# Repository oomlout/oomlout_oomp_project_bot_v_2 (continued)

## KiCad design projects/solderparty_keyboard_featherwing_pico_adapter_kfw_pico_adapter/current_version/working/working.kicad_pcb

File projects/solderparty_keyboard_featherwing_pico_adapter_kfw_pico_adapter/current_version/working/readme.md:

# keyboard_featherwing_pico_adapter
 
## summary 
* id: solderparty_keyboard_featherwing_pico_adapter_kfw_pico_adapter
* user: solderparty
* name: keyboard_featherwing_pico_adapter
* board: kfw_pico_adapter
* repo: https://github.com/solderparty/keyboard_featherwing_pico_adapter
* src_file_repo_kicad_pcb: kfw_pico_adapter.kicad_pcb
* src_file_repo_kicad_pcb_link: https://github.com/solderparty/keyboard_featherwing_pico_adapter/tree/main/kfw_pico_adapter.kicad_pcb
* src_file_repo_kicad_sch: kfw_pico_adapter.kicad_sch
* src_file_repo_kicad_sch_link: https://github.com/solderparty/keyboard_featherwing_pico_adapter/tree/main/kfw_pico_adapter.kicad_sch

* src_file_repo_sch: 
* src_file_repo_sch_link: https://github.com/solderparty/keyboard_featherwing_pico_adapter/tree/main/
* full details link: https://github.com/oomlout/oomlout_oomp_project_bot_v_2/tree/main/projects/solderparty_keyboard_featherwing_pico_adapter_kfw_pico_adapter/current_version/working  

## schematic  
  
[schematic (pdf)](working_schematic.pdf) 

## pcb  

[board (pdf)](working.pdf)  

## working_bom
| Id | Designator | Footprint | Quantity | Designation | Supplier and ref |  | None | 
| --- | --- | --- | --- | --- | --- | --- | --- | 
| 1 | J2 | PinHeader_2x16_P2.54mm_Vertical | 1 | Conn_Left |  |  | [''] | 
| 2 | J3 | PinHeader_2x12_P2.54mm_Vertical | 1 | Conn_Right |  |  | [''] | 
| 3 | G*** | SolderParty-New-Logo_15x12.7mm_SilkScreen | 1 | LOGO |  |  | [''] | 
| 4 | U1 | RaspberryPi_Pico | 1 | RaspberryPi_Pico |  |  | [''] | 
| 5 | G*** | SolderParty-New-Logo_7.5x6.4mm_SilkScreen | 1 | LOGO |  |  | [''] | 

## bom_schematic
| Ref | Qnty | Value | Cmp name | Footprint | Description | Vendor | DNP | 
| --- | --- | --- | --- | --- | --- | --- | --- | 
| J2 | 1 | Conn_Left | Conn_02x16_Odd_Even | Connector_PinHeader_2.54mm:PinHeader_2x16_P2.54mm_Vertical | Generic connector, double row, 02x16, odd/even pin numbering scheme (row 1 odd numbers, row 2 even numbers), script generated (kicad-library-utils/schlib/autogen/connector/) |  |  | 
| J3 | 1 | Conn_Right | Conn_02x12_Odd_Even | Connector_PinHeader_2.54mm:PinHeader_2x12_P2.54mm_Vertical | Generic connector, double row, 02x12, odd/even pin numbering scheme (row 1 odd numbers, row 2 even numbers), script generated (kicad-library-utils/schlib/autogen/connector/) |  |  | 
| U1 | 1 | RaspberryPi_Pico | RaspberryPi_Pico | Module_Extra:RaspberryPi_Pico |  |  |  |

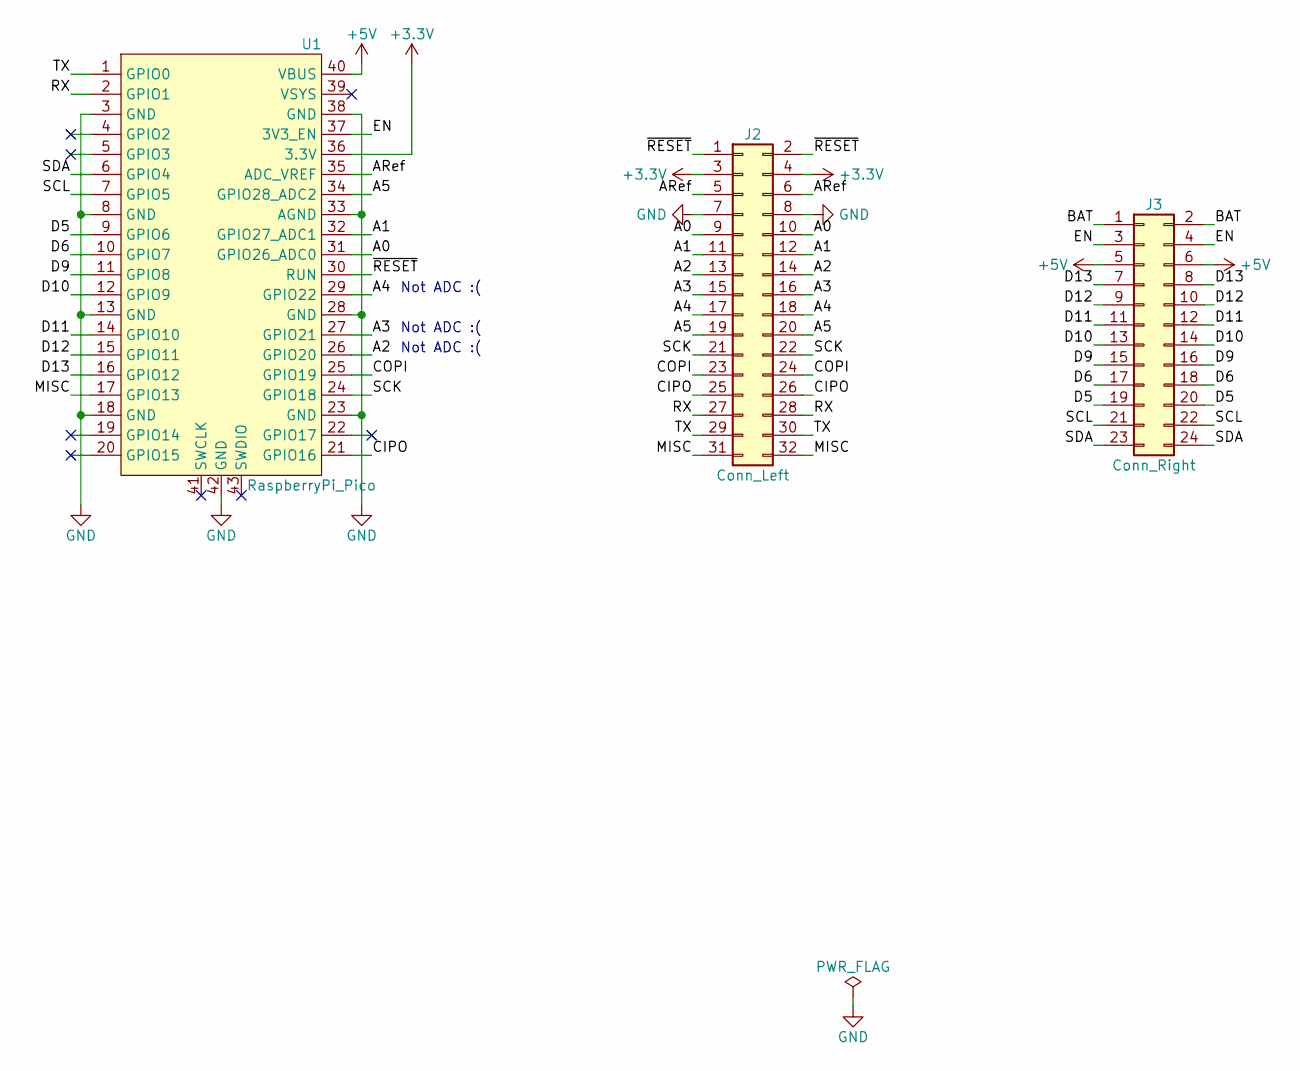
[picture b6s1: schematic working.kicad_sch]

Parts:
J2: Conn_Left; PinHeader_2x16_P2.54mm_Vertical
J3: Conn_Right; PinHeader_2x12_P2.54mm_Vertical
U1: RaspberryPi_Pico

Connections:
+3V3: J2.3, J2.4, U1.36 (3.3V)
+5V: J3.5, J3.6, U1.40 (VBUS)
/A0: J2.9, J2.10, U1.31 (GPIO26_ADC0)
/A1: J2.11, J2.12, U1.32 (GPIO27_ADC1)
/A2: J2.13, J2.14, U1.26 (GPIO20)
/A3: J2.15, J2.16, U1.27 (GPIO21)
/A4: J2.17, J2.18, U1.29 (GPIO22)
/A5: J2.19, J2.20, U1.34 (GPIO28_ADC2)
/ARef: J2.5, J2.6, U1.35 (ADC_VREF)
/BAT: J3.1, J3.2
/CIPO: J2.25, J2.26, U1.21 (GPIO16)
/COPI: J2.23, J2.24, U1.25 (GPIO19)
/D5: J3.19, J3.20, U1.9 (GPIO6)
/D6: J3.17, J3.18, U1.10 (GPIO7)
/D9: J3.15, J3.16, U1.11 (GPIO8)
/D10: J3.13, J3.14, U1.12 (GPIO9)
/D11: J3.11, J3.12, U1.14 (GPIO10)
/D12: J3.9, J3.10, U1.15 (GPIO11)
/D13: J3.7, J3.8, U1.16 (GPIO12)
/EN: J3.3, J3.4, U1.37 (3V3_EN)
/MISC: J2.31, J2.32, U1.17 (GPIO13)
/RX: J2.27, J2.28, U1.2 (GPIO1)
/SCK: J2.21, J2.22, U1.24 (GPIO18)
/SCL: J3.21, J3.22, U1.7 (GPIO5)
/SDA: J3.23, J3.24, U1.6 (GPIO4)
/TX: J2.29, J2.30, U1.1 (GPIO0)
/~RESET: J2.1, J2.2, U1.30 (RUN)
GND: J2.7, J2.8, U1.3 (GND), U1.8 (GND), U1.13 (GND), U1.18 (GND), U1.23 (GND), U1.28 (GND), U1.33 (AGND), U1.38 (GND), U1.42 (GND)

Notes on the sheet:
Not ADC :(

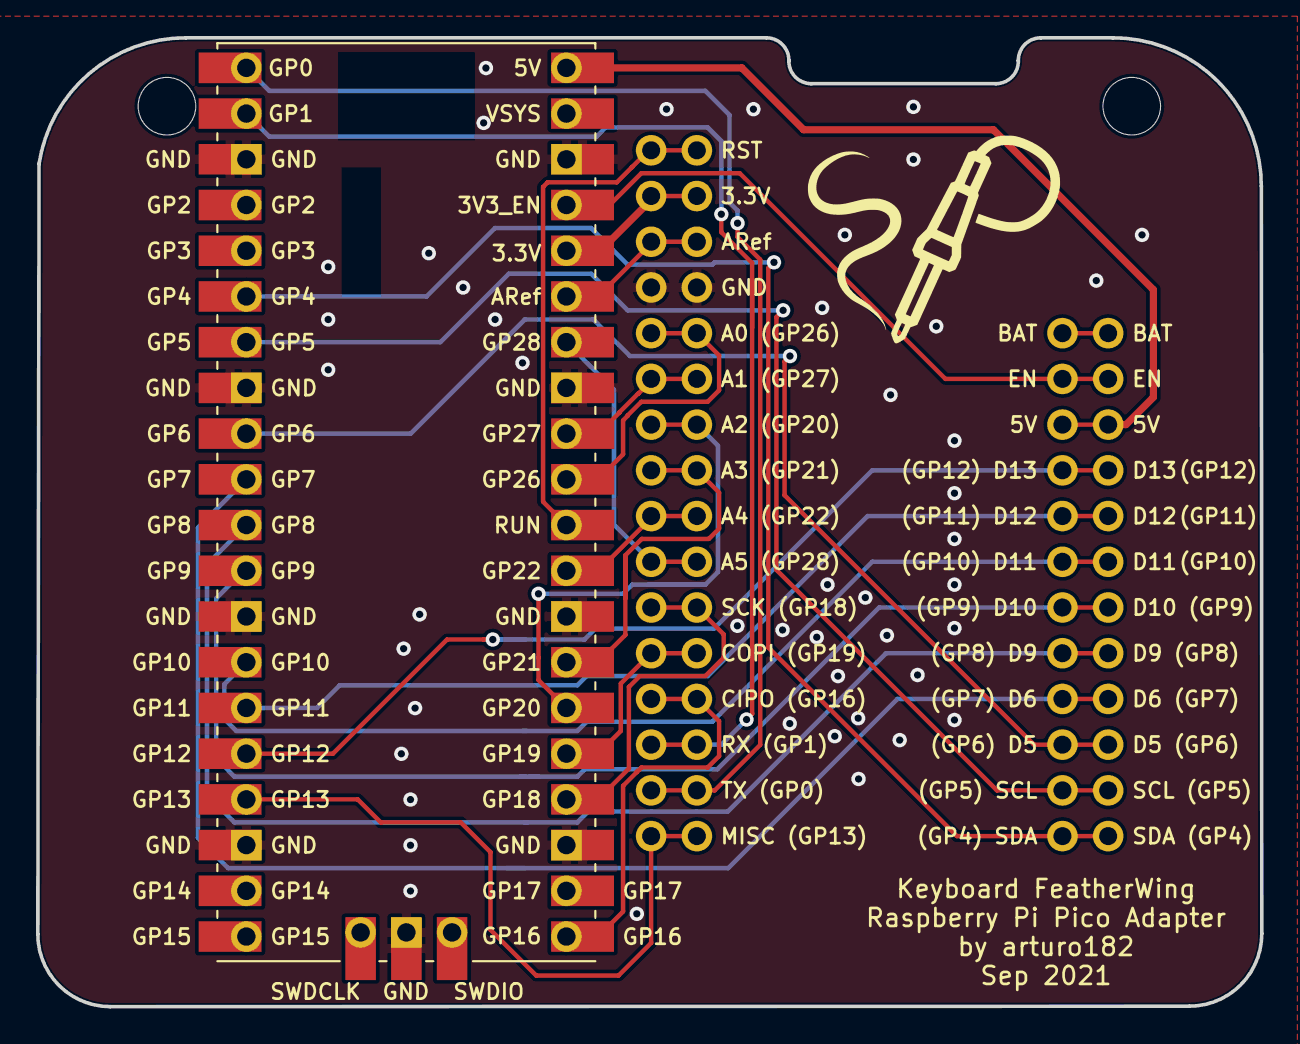
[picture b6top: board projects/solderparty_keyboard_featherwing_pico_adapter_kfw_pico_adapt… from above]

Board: 2 copper layers, 68.0 x 53.8 mm, 3 parts (0 on the bottom side), 28 nets.

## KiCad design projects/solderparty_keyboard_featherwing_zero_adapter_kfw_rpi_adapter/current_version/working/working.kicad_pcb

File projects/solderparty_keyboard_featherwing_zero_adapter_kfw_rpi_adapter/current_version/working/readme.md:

# keyboard_featherwing_zero_adapter
 
## summary 
* id: solderparty_keyboard_featherwing_zero_adapter_kfw_rpi_adapter
* user: solderparty
* name: keyboard_featherwing_zero_adapter
* board: kfw_rpi_adapter
* repo: https://github.com/solderparty/keyboard_featherwing_zero_adapter
* src_file_repo_kicad_pcb: kfw_rpi_adapter.kicad_pcb
* src_file_repo_kicad_pcb_link: https://github.com/solderparty/keyboard_featherwing_zero_adapter/tree/main/kfw_rpi_adapter.kicad_pcb
* src_file_repo_kicad_sch: kfw_rpi_adapter.kicad_sch
* src_file_repo_kicad_sch_link: https://github.com/solderparty/keyboard_featherwing_zero_adapter/tree/main/kfw_rpi_adapter.kicad_sch

* src_file_repo_sch: 
* src_file_repo_sch_link: https://github.com/solderparty/keyboard_featherwing_zero_adapter/tree/main/
* full details link: https://github.com/oomlout/oomlout_oomp_project_bot_v_2/tree/main/projects/solderparty_keyboard_featherwing_zero_adapter_kfw_rpi_adapter/current_version/working  

## schematic  
  
[schematic (pdf)](working_schematic.pdf) 

## pcb  

[board (pdf)](working.pdf)  

## working_bom
| Id | Designator | Footprint | Quantity | Designation | Supplier and ref |  | None | 
| --- | --- | --- | --- | --- | --- | --- | --- | 
| 1 | U1 | TSSOP-10_3x3mm_P0.5mm | 1 | ADS1115IDGS |  |  | [''] | 
| 2 | G***,G*** | SolderParty-New-Logo_20x16.9mm_SilkScreen | 2 | LOGO |  |  | [''] | 
| 3 | JP1 | SolderJumper-3_P1.3mm_Bridged12_RoundedPad1.0x1.5mm_NumberLabels | 1 | SJ_STM_KBD |  |  | [''] | 
| 4 | REF**,REF** | Fiducial_0.5mm_Mask1.5mm | 2 | Fiducial_0.5mm_Mask1.5mm |  |  | [''] | 
| 5 | J2 | PinHeader_2x16_P2.54mm_Vertical | 1 | Conn_Left |  |  | [''] | 
| 6 | J3 | PinHeader_2x12_P2.54mm_Vertical | 1 | Conn_Right |  |  | [''] | 
| 7 | C1 | C_0603_1608Metric | 1 | 0.1uF |  |  | [''] | 
| 8 | J1 | PinHeader_2x20_P2.54mm_Vertical | 1 | Conn_RPi |  |  | [''] | 

## bom_schematic
| Ref | Qnty | Value | Cmp name | Footprint | Description | Vendor | DNP | 
| --- | --- | --- | --- | --- | --- | --- | --- | 
| C1 | 1 | 0.1uF | C_Small | Capacitor_SMD:C_0603_1608Metric | Unpolarized capacitor, small symbol |  |  | 
| J1 | 1 | Conn_RPi | Conn_02x20_Odd_Even | Connector_PinHeader_2.54mm:PinHeader_2x20_P2.54mm_Vertical | Generic connector, double row, 02x20, odd/even pin numbering scheme (row 1 odd numbers, row 2 even numbers), script generated (kicad-library-utils/schlib/autogen/connector/) |  |  | 
| J2 | 1 | Conn_Left | Conn_02x16_Odd_Even | Connector_PinHeader_2.54mm:PinHeader_2x16_P2.54mm_Vertical | Generic connector, double row, 02x16, odd/even pin numbering scheme (row 1 odd numbers, row 2 even numbers), script generated (kicad-library-utils/schlib/autogen/connector/) |  |  | 
| J3 | 1 | Conn_Right | Conn_02x12_Odd_Even | Connector_PinHeader_2.54mm:PinHeader_2x12_P2.54mm_Vertical | Generic connector, double row, 02x12, odd/even pin numbering scheme (row 1 odd numbers, row 2 even numbers), script generated (kicad-library-utils/schlib/autogen/connector/) |  |  | 
| JP1 | 1 | SJ_STM_KBD | SolderJumper_3_Bridged12 | Jumper:SolderJumper-3_P1.3mm_Bridged12_RoundedPad1.0x1.5mm_NumberLabels | 3-pole Solder Jumper, pins 1+2 closed/bridged |  |  | 
| U1 | 1 | ADS1115IDGS | ADS1115IDGS | Package_SO:TSSOP-10_3x3mm_P0.5mm | Ultra-Small, Low-Power, I2C-Compatible, 860-SPS, 16-Bit ADCs With Internal Reference, Oscillator, and Programmable Comparator, VSSOP-10 |  |  |

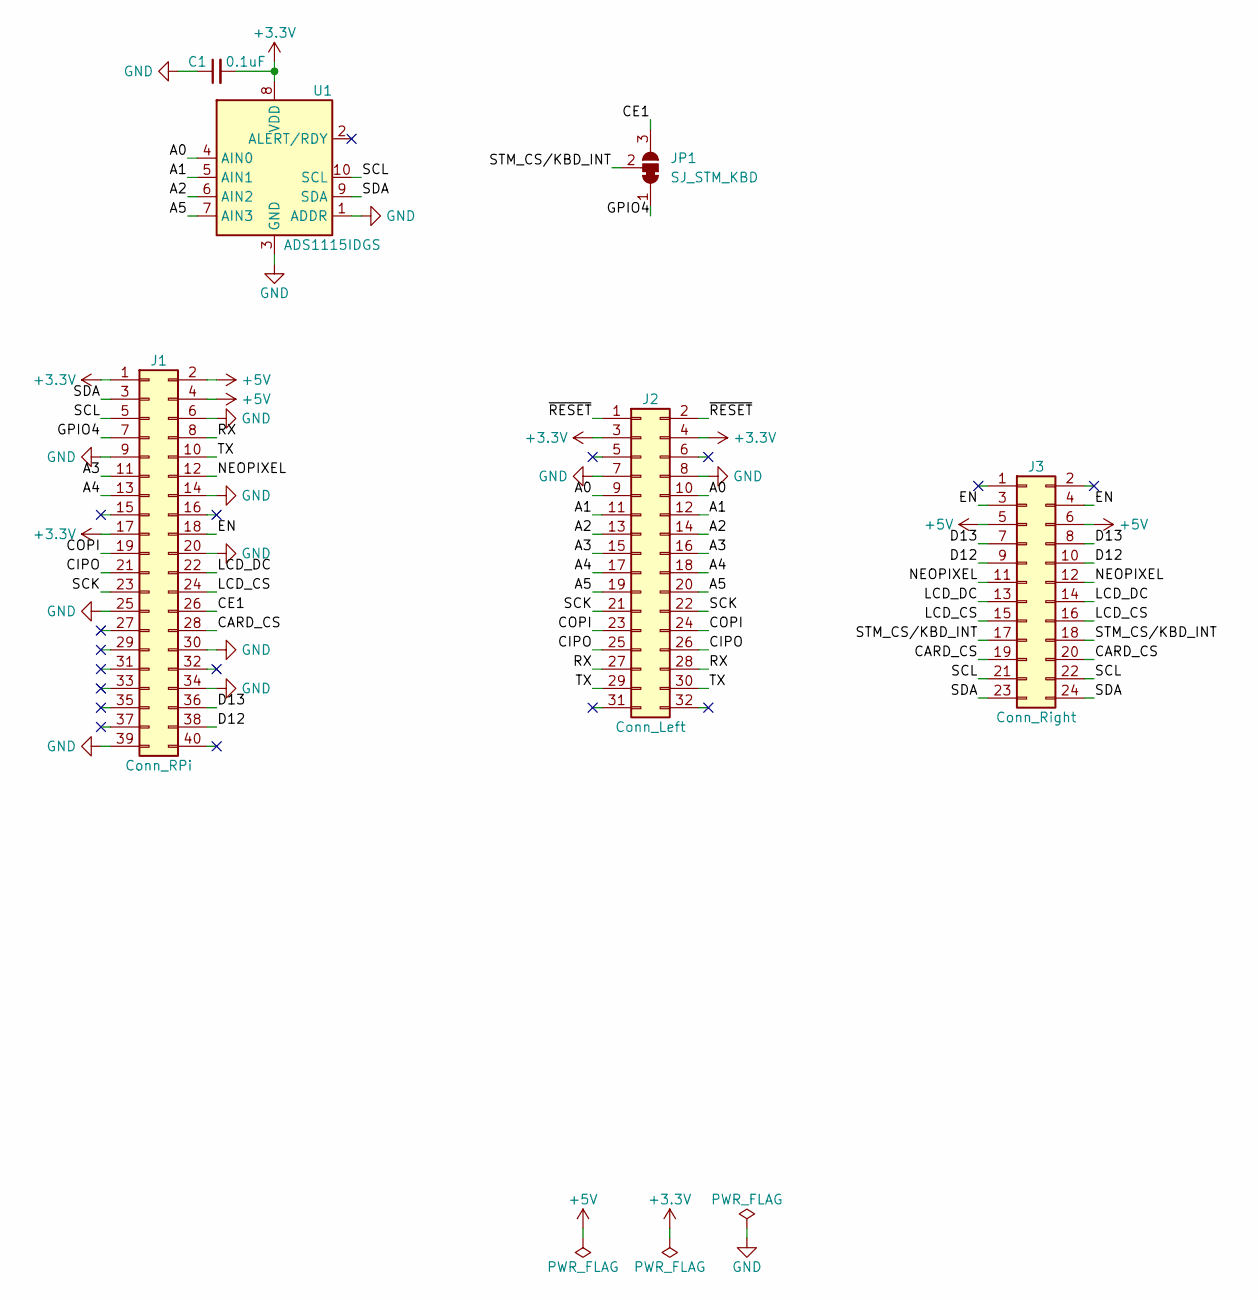
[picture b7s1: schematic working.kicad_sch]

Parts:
C1: 0.1uF; C_0603_1608Metric
J1: Conn_RPi; PinHeader_2x20_P2.54mm_Vertical
J2: Conn_Left; PinHeader_2x16_P2.54mm_Vertical
J3: Conn_Right; PinHeader_2x12_P2.54mm_Vertical
JP1: SJ_STM_KBD; SolderJumper-3_P1.3mm_Bridged12_RoundedPad1.0x1.5mm_NumberL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
U1: ADS1115IDGS; TSSOP-10_3x3mm_P0.5mm

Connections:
+3V3: C1.2, J1.1, J1.17, J2.3, J2.4, U1.8 (VDD)
+5V: J1.2, J1.4, J3.5, J3.6
/A0: J2.9, J2.10, U1.4 (AIN0)
/A1: J2.11, J2.12, U1.5 (AIN1)
/A2: J2.13, J2.14, U1.6 (AIN2)
/A3: J1.11, J2.15, J2.16
/A4: J1.13, J2.17, J2.18
/A5: J2.19, J2.20, U1.7 (AIN3)
/CARD_CS: J1.28, J3.19, J3.20
/CE1: J1.26, JP1.3 (B)
/CIPO: J1.21, J2.25, J2.26
/COPI: J1.19, J2.23, J2.24
/D12: J1.38, J3.9, J3.10
/D13: J1.36, J3.7, J3.8
/EN: J1.18, J3.3, J3.4
/GPIO4: J1.7, JP1.1 (A)
/LCD_CS: J1.24, J3.15, J3.16
/LCD_DC: J1.22, J3.13, J3.14
/NEOPIXEL: J1.12, J3.11, J3.12
/RX: J1.8, J2.27, J2.28
/SCK: J1.23, J2.21, J2.22
/SCL: J1.5, J3.21, J3.22, U1.10 (SCL)
/SDA: J1.3, J3.23, J3.24, U1.9 (SDA)
/STM_CS/KBD_INT: J3.17, J3.18, JP1.2 (C)
/TX: J1.10, J2.29, J2.30
/~RESET: J2.1, J2.2
GND: C1.1, J1.6, J1.9, J1.14, J1.20, J1.25, J1.30, J1.34, J1.39, J2.7, J2.8, U1.1 (ADDR), U1.3 (GND)

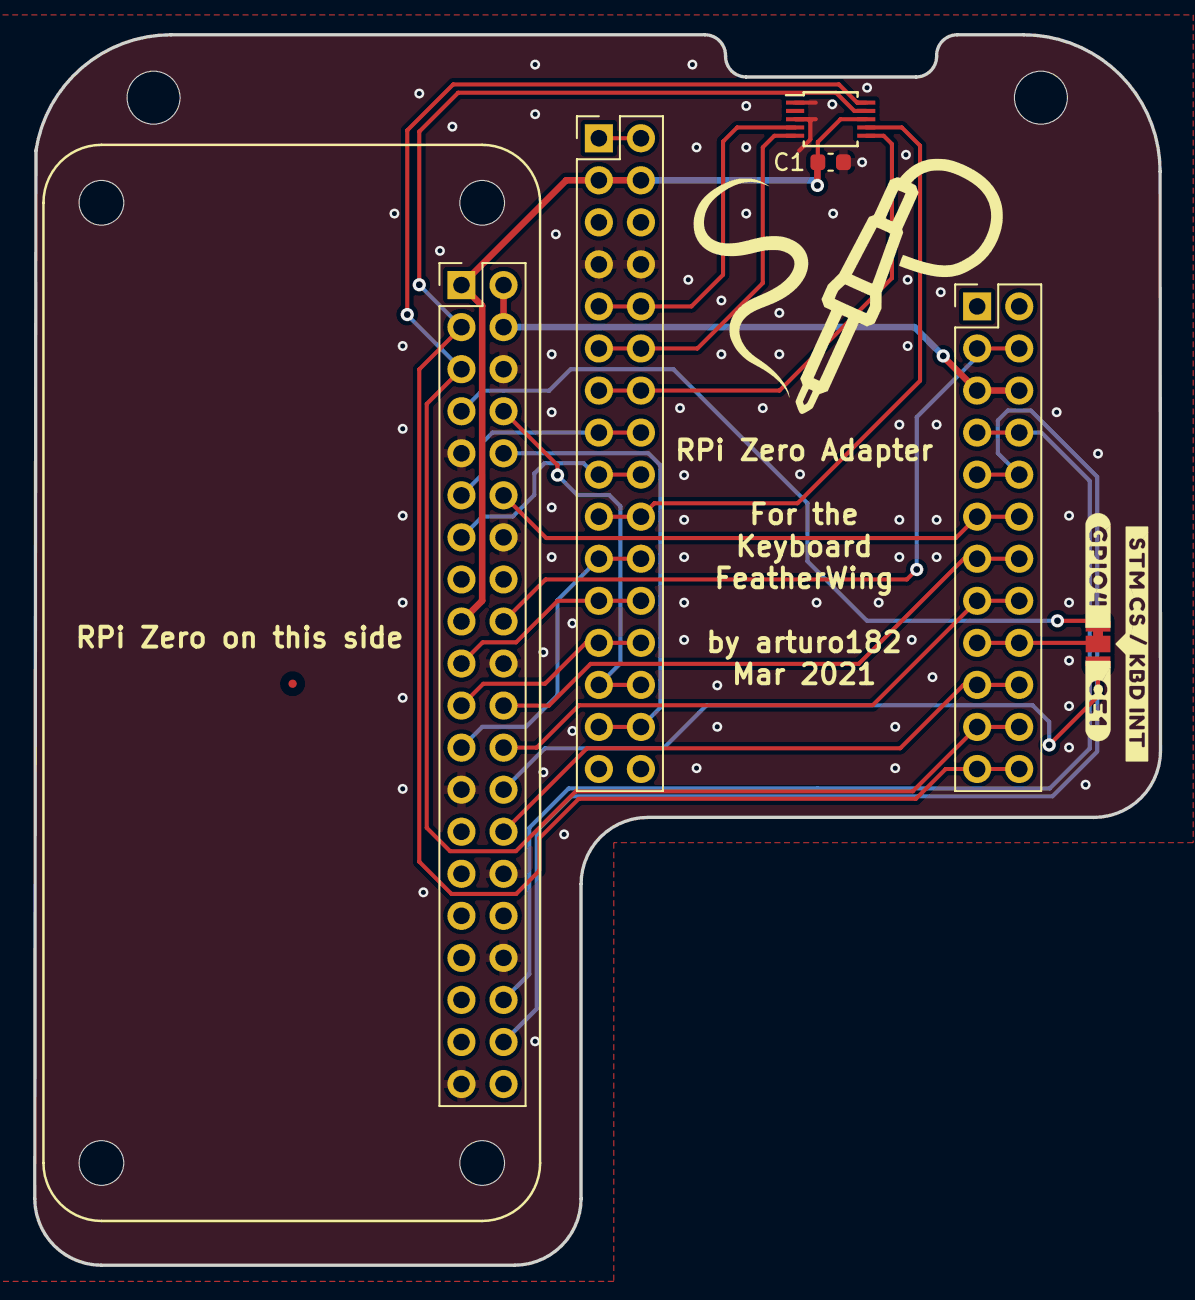
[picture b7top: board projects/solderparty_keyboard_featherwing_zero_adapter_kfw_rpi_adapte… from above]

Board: 2 copper layers, 68.0 x 74.3 mm, 6 parts (0 on the bottom side), 27 nets.
